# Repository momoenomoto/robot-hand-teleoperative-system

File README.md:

# robot-hand-teleoperative-system

Wireless glove controlled robotic hand using BLE 5 and STM32F7 MCU with Cortex-M7

This repository contains my EENG-SHU 400 Senior Capstone Design Project. The code is written, compiled, and flashed in Keil µVision 5.0.

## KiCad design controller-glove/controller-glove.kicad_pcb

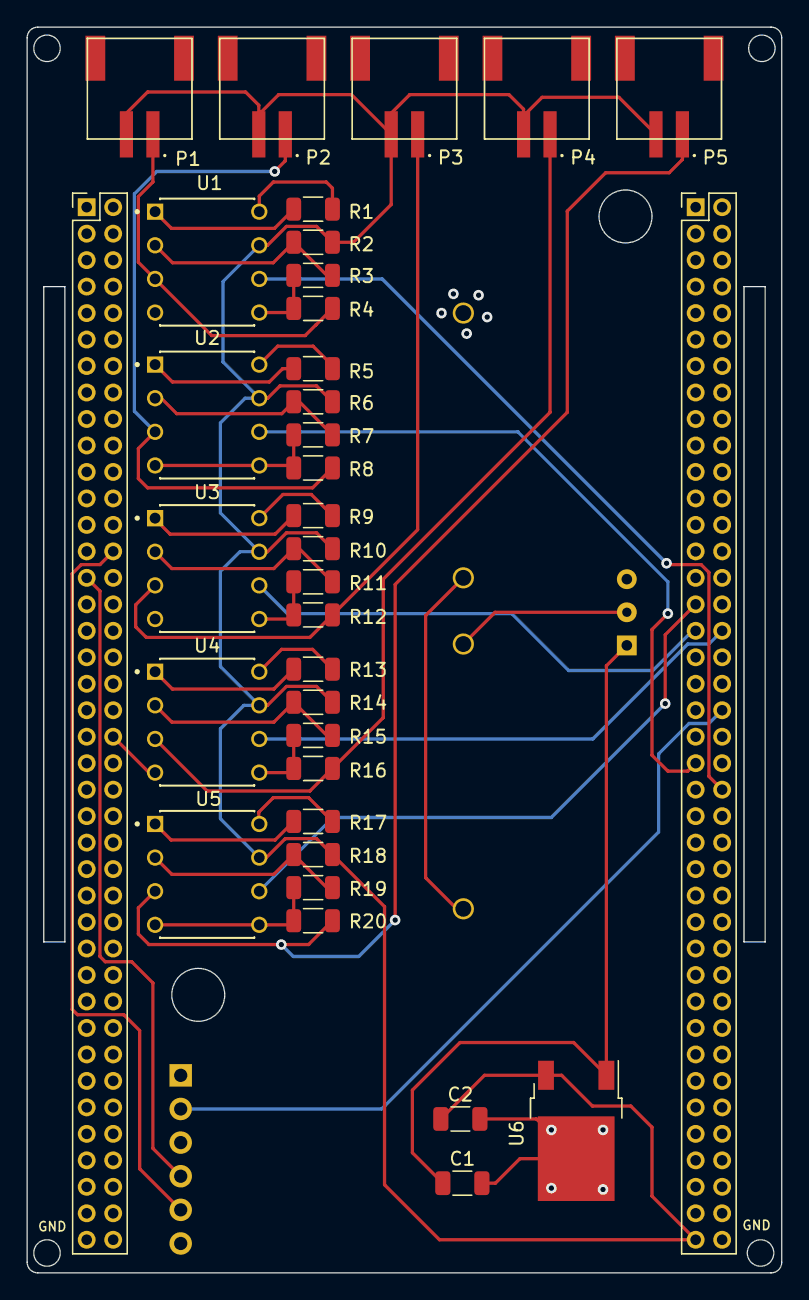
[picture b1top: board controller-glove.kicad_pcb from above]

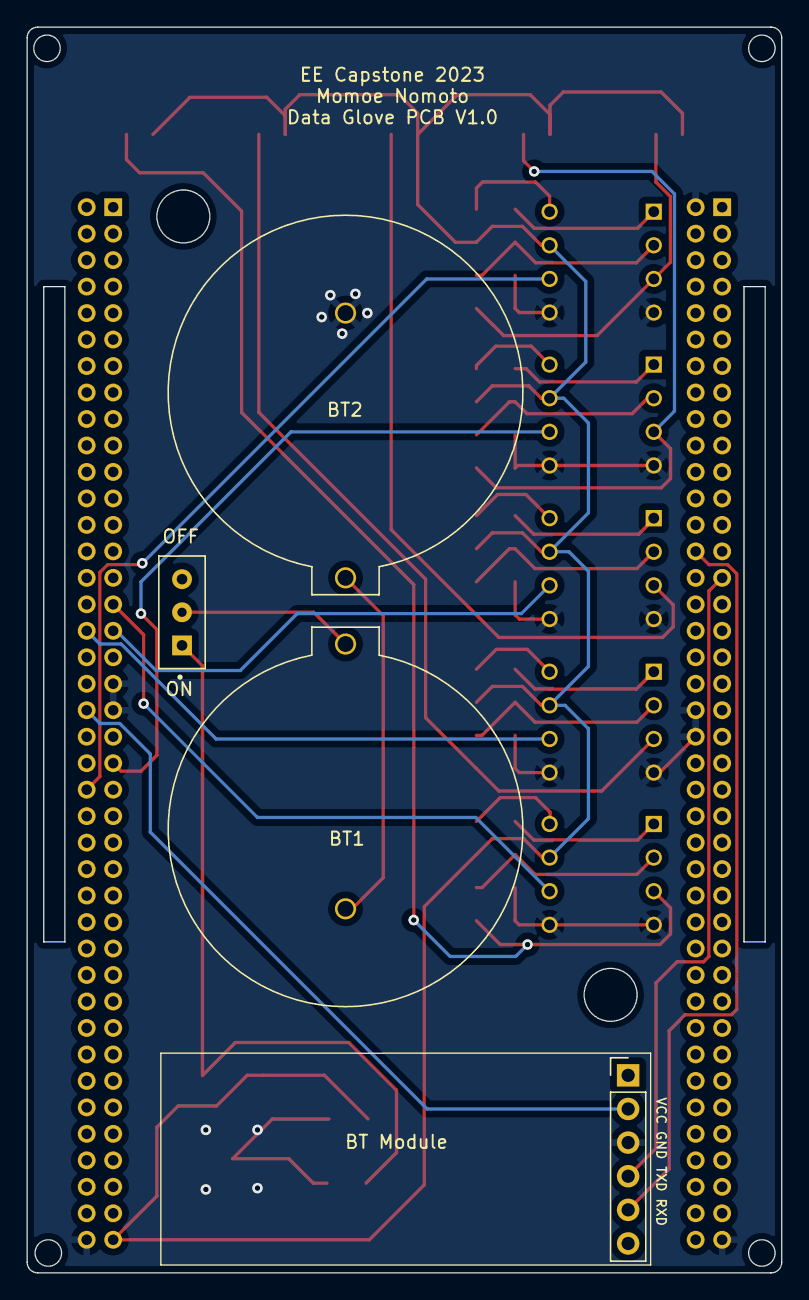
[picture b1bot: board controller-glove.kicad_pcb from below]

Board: 2 copper layers, 57.0 x 94.1 mm, 39 parts (4 on the bottom side), 33 nets.

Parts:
BT1, BT2: CR2450
C1: 0.33uF; C_1206_3216Metric
C2: 0.1uF; C_1206_3216Metric
J1: Conn_02x40_Odd_Even_Left; PinHeader_2x40_P2.00mm_Vertical
J2: Conn_02x40_Odd_Even_Right; PinHeader_2x40_P2.00mm_Vertical
J3: Conn_01x06_Female; PinHeader_1x06_P2.54mm_Vertical
P1, P2, P3, P4, P5: S2B-PH-SM4-TB; JST_S2B-PH-SM4-TB
R1, R2, R3, R4, R5, R6, R7, R8, R9, R10, R11, R12, R13, R14, R15, R16, R17, R18, R19, R20: R; R_1206_3216Metric
S1: 500SSP1S2M2QEA; SW_500SSP1S2M2QEA
U1, U2, U3, U4, U5: AD620; DIP787W46P254L1016H533Q8
U6: LM7805_TO220; TO-252-2

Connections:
+3.3V: J2.40, J3.2
+5V: C2.1, J2.79, P1.2, P2.2, P3.2, P4.2, P5.2, R2.2, R6.2, R10.2, R14.2, R18.2, U1.7 (Vs+), U2.7 (Vs+), U3.7 (Vs+), U4.7 (Vs+), U5.7 (Vs+), U6.3 (VO)
/Conditioning_Circuit1/OUTPUT: J2.43, U2.6
/Conditioning_Circuit1/S1: P2.1, R8.2, U2.3 (+)
/Conditioning_Circuit2/OUTPUT: J2.33, U3.6
/Conditioning_Circuit2/S1: P3.1, R12.2, U3.3 (+)
/Conditioning_Circuit3/OUTPUT: J2.34, U4.6
/Conditioning_Circuit3/S1: P4.1, R16.2, U4.3 (+)
/Conditioning_Circuit4/OUTPUT: J2.31, U5.6
/Conditioning_Circuit4/S1: P5.1, R20.2, U5.3 (+)
/Conditioning_Circuit/OUTPUT: J2.46, U1.6
/Conditioning_Circuit/S1: P1.1, R4.2, U1.3 (+)
GND: BT2.N, C1.2, C2.2, J1.2, J1.40, J1.42, J1.79, J2.37, J2.39, J2.80, J3.3, R3.1, R4.1, R7.1, R8.1, R11.1, R12.1, R15.1, R16.1, R19.1, R20.1, U1.4 (Vs-), U1.5 (Ref), U2.4 (Vs-), U2.5 (Ref), U3.4 (Vs-), U3.5 (Ref), U4.4 (Vs-), U4.5 (Ref), U5.4 (Vs-), U5.5 (Ref), U6.2 (GND)
unnamed: BT1.N, BT2.P
unnamed: BT1.P, S1.2
unnamed: C1.1, S1.1, U6.1 (VI)
unnamed: J1.28, J3.5
unnamed: J1.29, J3.4
unnamed: R1.1, U1.1 (Rg)
unnamed: R1.2, U1.8 (Rg)
unnamed: R2.1, R3.2, U1.2 (-)
unnamed: R5.1, U2.1 (Rg)
unnamed: R5.2, U2.8 (Rg)
unnamed: R6.1, R7.2, U2.2 (-)
unnamed: R9.1, U3.1 (Rg)
unnamed: R9.2, U3.8 (Rg)
unnamed: R10.1, R11.2, U3.2 (-)
unnamed: R13.1, U4.1 (Rg)
unnamed: R13.2, U4.8 (Rg)
unnamed: R14.1, R15.2, U4.2 (-)
unnamed: R17.1, U5.1 (Rg)
unnamed: R17.2, U5.8 (Rg)
unnamed: R18.1, R19.2, U5.2 (-)

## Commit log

2023-03-11 added main files for robot hand with rtos included
2023-03-15 fixed servo thread issue and message queue
2023-03-15 configure data glove project
2023-03-15 edit irq handler
2023-03-16 add lcd display string and rtos
2023-03-17 change main to use rtos
2023-03-17 tried to add dma for multiple adc channels
2023-03-19 edit dma configuration
2023-03-20 change priority of thread and definitions
2023-03-20 update driver and systick handler
2023-03-20 adc+dma works with 2 channels now
2023-03-20 enabled all four adc channels
2023-03-20 5 sensors set up
2023-03-20 bug on lcd
2023-03-22 edit flags
2023-03-22 cleaner code
2023-03-22 added a very not fine filter but there is very minimal jitter
2023-03-22 increase frequency
2023-03-22 change threshold
2023-03-22 leave out LSB
2023-04-21 modify parameters and clean up code
2023-04-28 change timer frequency
2023-04-28 modifications to servo
2023-05-03 adjust thresholds
2023-05-15 add kicad files
2023-05-15 add presentation slides
